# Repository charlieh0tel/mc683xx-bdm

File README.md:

# mc683xx-bdm

A USB background debug mode (BDM) pod for Motorola CPU32
microcontrollers (683xx), such as the MC68331. A Raspberry Pi Pico on a
small carrier board drives the standard 10-pin BDM header through 5 V
level translators. Firmware and host tools are in Rust.

- Reset, halt, run and step the target; read and write its registers
  and memory.
- Debug with gdb: breakpoints, stepping, Ctrl-C.
- Script it from Python, flash programming included.
- Read 512 KB in under 6 seconds.

Proven on an MC68331 from a Linux host; see [docs/status.md](docs/status.md)
for what works, what is untried, and the limits.

## Quickstart

1. Install `bdm`, the udev rule and the firmware, from the
   [APT repository](https://github.com/charlieh0tel/apt-repo)
   (`sudo apt-get install mc683xx-bdm`) or a GitHub Release's `.deb`.
2. Flash the firmware: `bdm bootsel`, then copy
   `/usr/share/mc683xx-bdm/pod-fw-rp2040.uf2` onto the RPI-RP2 drive.
3. Cable the pod to the target's BDM header and power the target.
4. Run `bdm pins`, `bdm reset`, then `bdm regs`.

Don't unplug the pod while its green LED is lit.

## Install

```
sudo apt-get install mc683xx-bdm   # bdm, the udev rule, the UF2
cargo install mc683xx-bdm          # bdm only
pip install mc683xx-bdm            # the Python module mc683xx_bdm
```

Without the Debian package, install the udev rule by hand
([docs/usage.md](docs/usage.md)).

## Documentation

- [docs/usage.md](docs/usage.md): `bdm`, gdb, Python, udev.
- [docs/status.md](docs/status.md): what works, limits, getting a board.
- [docs/development.md](docs/development.md): layout, building, testing.
- [docs/usb-protocol.md](docs/usb-protocol.md): the host-pod protocol.
- [docs/bring-up.md](docs/bring-up.md): checking a new pod.
- [hardware/README.md](hardware/README.md): the carrier's revisions.
- [PLAN.md](PLAN.md): the design and why.

## License

Hardware (`hardware/`): CERN-OHL-S-2.0. Everything else of the
project's own: GPL-3.0-only. `third_party/` documents are their
owners' (`third_party/NOTICE`).

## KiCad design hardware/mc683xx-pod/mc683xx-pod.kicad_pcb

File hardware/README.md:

# Hardware

`mc683xx-pod/` is the carrier board's KiCad project.  `production/`
holds each release as fabricated; it is not changed afterwards.

## Revisions

| Rev | Release | PCB | Assembly |
|---|---|---|---|
| 0.1 | `production/20261102-0.1/` | as 0.2 | A1 (Pico) not in the BOM, hand-soldered; J2 (SWD) fitted |
| 0.2 | `production/20261102-0.2/` | as 0.1 | A1 placed by JLCPCB (LCSC C9900019762); J2 not fitted |

0.1 and 0.2 are one PCB: their Gerbers and drill files match, apart
from creation dates.  The revision differs only in the BOM, the
placement file and the title blocks.  The silkscreen of both reads
"mc683xx-pod rev 0.1", since the silkscreen text was not bumped for
0.2.  A board with a Pico but no J2 is a 0.2.

## Next revision

Changes for the carrier after 0.2.  None is needed for 0.2 to work;
each fixes something seen on the bench.

1. BKPT released whatever the Pico does.  A Pico reset or power loss
   while U1 is enabled can glitch BKPT (`docs/bring-up.md`, step 5):
   GP9, U1's input, falls through R15 and the RP2040's pull-down in
   about 0.3 us, before Q3's gate, through its 100k, turns U1 off in
   about 1-2 us; U1 drives BKPT low, then R3 pulls it high, one DSCLK
   clock to a halted CPU.  The firmware keeps U1 off while idle, which
   leaves only a reset mid-request or during `hold`.  Fix: drive U1's
   input through an inverting stage like Q3's, a BSS138BK with its
   gate on GP9 (100k gate pull-down) and its drain on U1's input with
   a 2.2k pull-up to target VDD; R15 goes.  Every state that leaves
   GP9 undriven or low (reset, boot, power loss, unpowered) then holds
   U1's input high, BKPT released, whatever U1's enable does.  The
   firmware inverts GP9 (its pad's output override).  Check: the
   stage's edges at 4 MHz DSCLK (about 20 ns into U1's input and the
   FET's output capacitance) and 2.3 mA from VDD while DSCLK is low.
2. Silkscreen revision text bumped with the title blocks
   (`AGENTS.md`, Hardware).
3. Status LEDs on the carrier, visible with the Pico mounted (a pod
   in a case may hide the Pico's GP25 LED, lit while U1 is on).
   Required: target VDD, lit while the target is powered.  Either
   wired straight from target VDD (works with the pod unpowered; loads
   target VDD a few mA) or driven by the firmware from the VDD sense
   reading (no load on the target; needs a spare GPIO).  Optional, on
   one or two more LEDs (mono, bicolor or tricolor, not decided),
   driven by the firmware from spare GPIOs: target halted (FREEZE
   high) or running (FREEZE low, also with no target); safe or not
   safe to remove (U1 off or on).  Pins: one GPIO per LED or color,
   from the spare GPIOs (GP0, GP1, GP13-GP22, GP27, GP28; PLAN.md, pin
   table).  With item 1's inverting stage a replug is always safe, so
   that indication could show activity or errors instead.

`fastcheck.py` reports on the BDM link's fast nets
(`uv run python fastcheck.py mc683xx-pod/mc683xx-pod.kicad_pcb`).
`make render` (repository root) rebuilds `docs/images/mc683xx-pod-top.png`
from the board file.

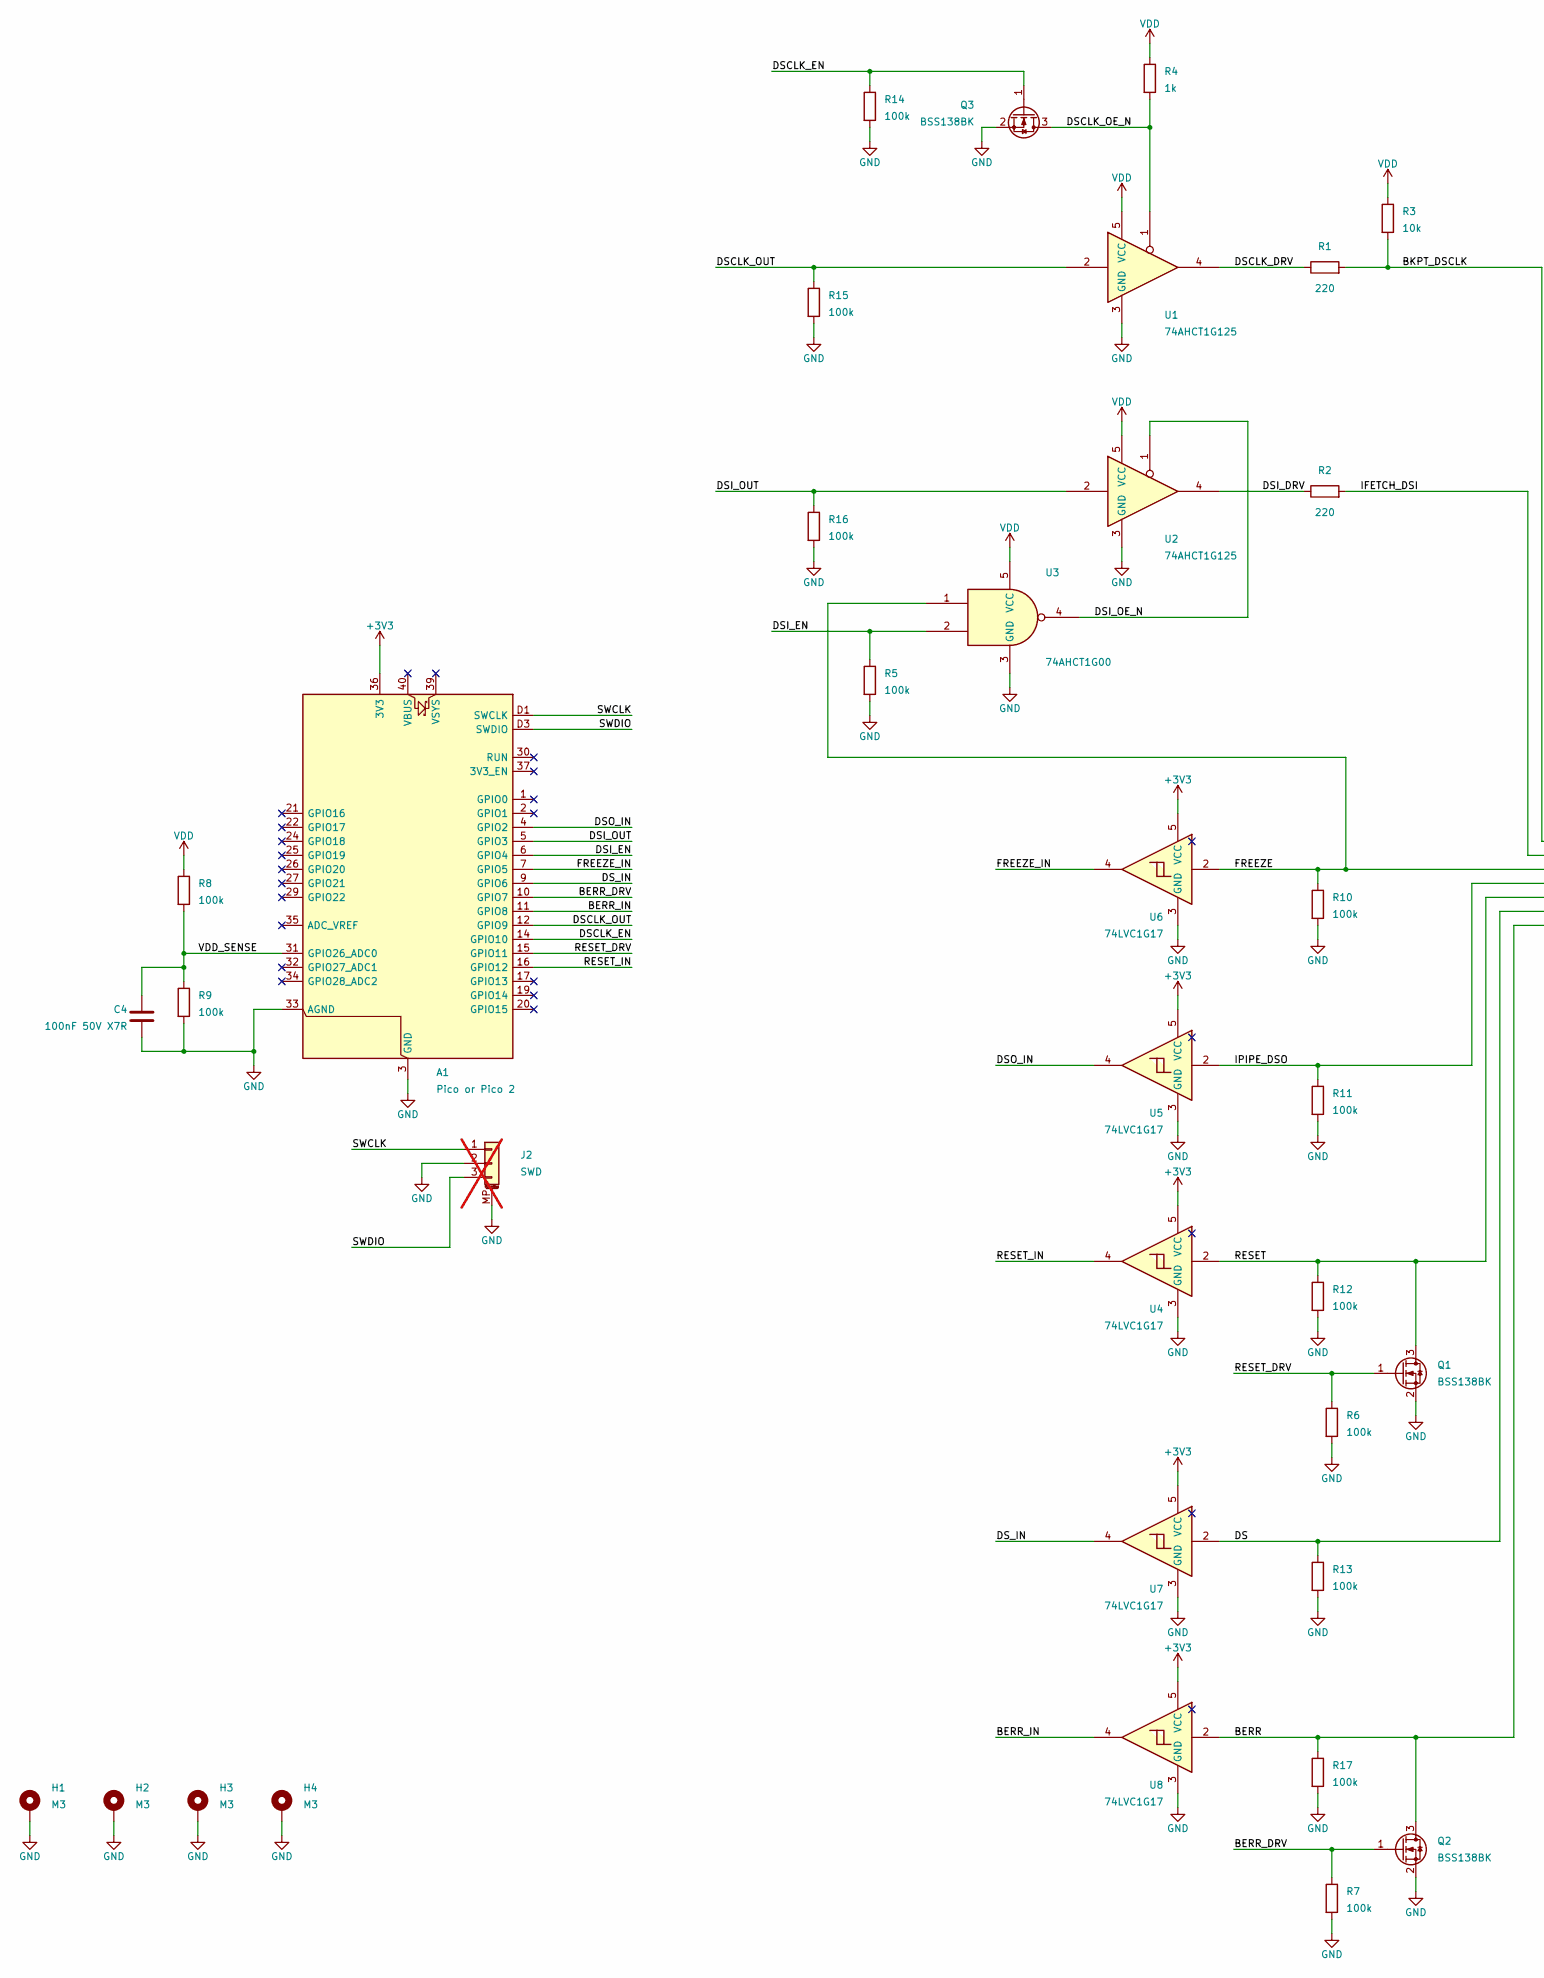
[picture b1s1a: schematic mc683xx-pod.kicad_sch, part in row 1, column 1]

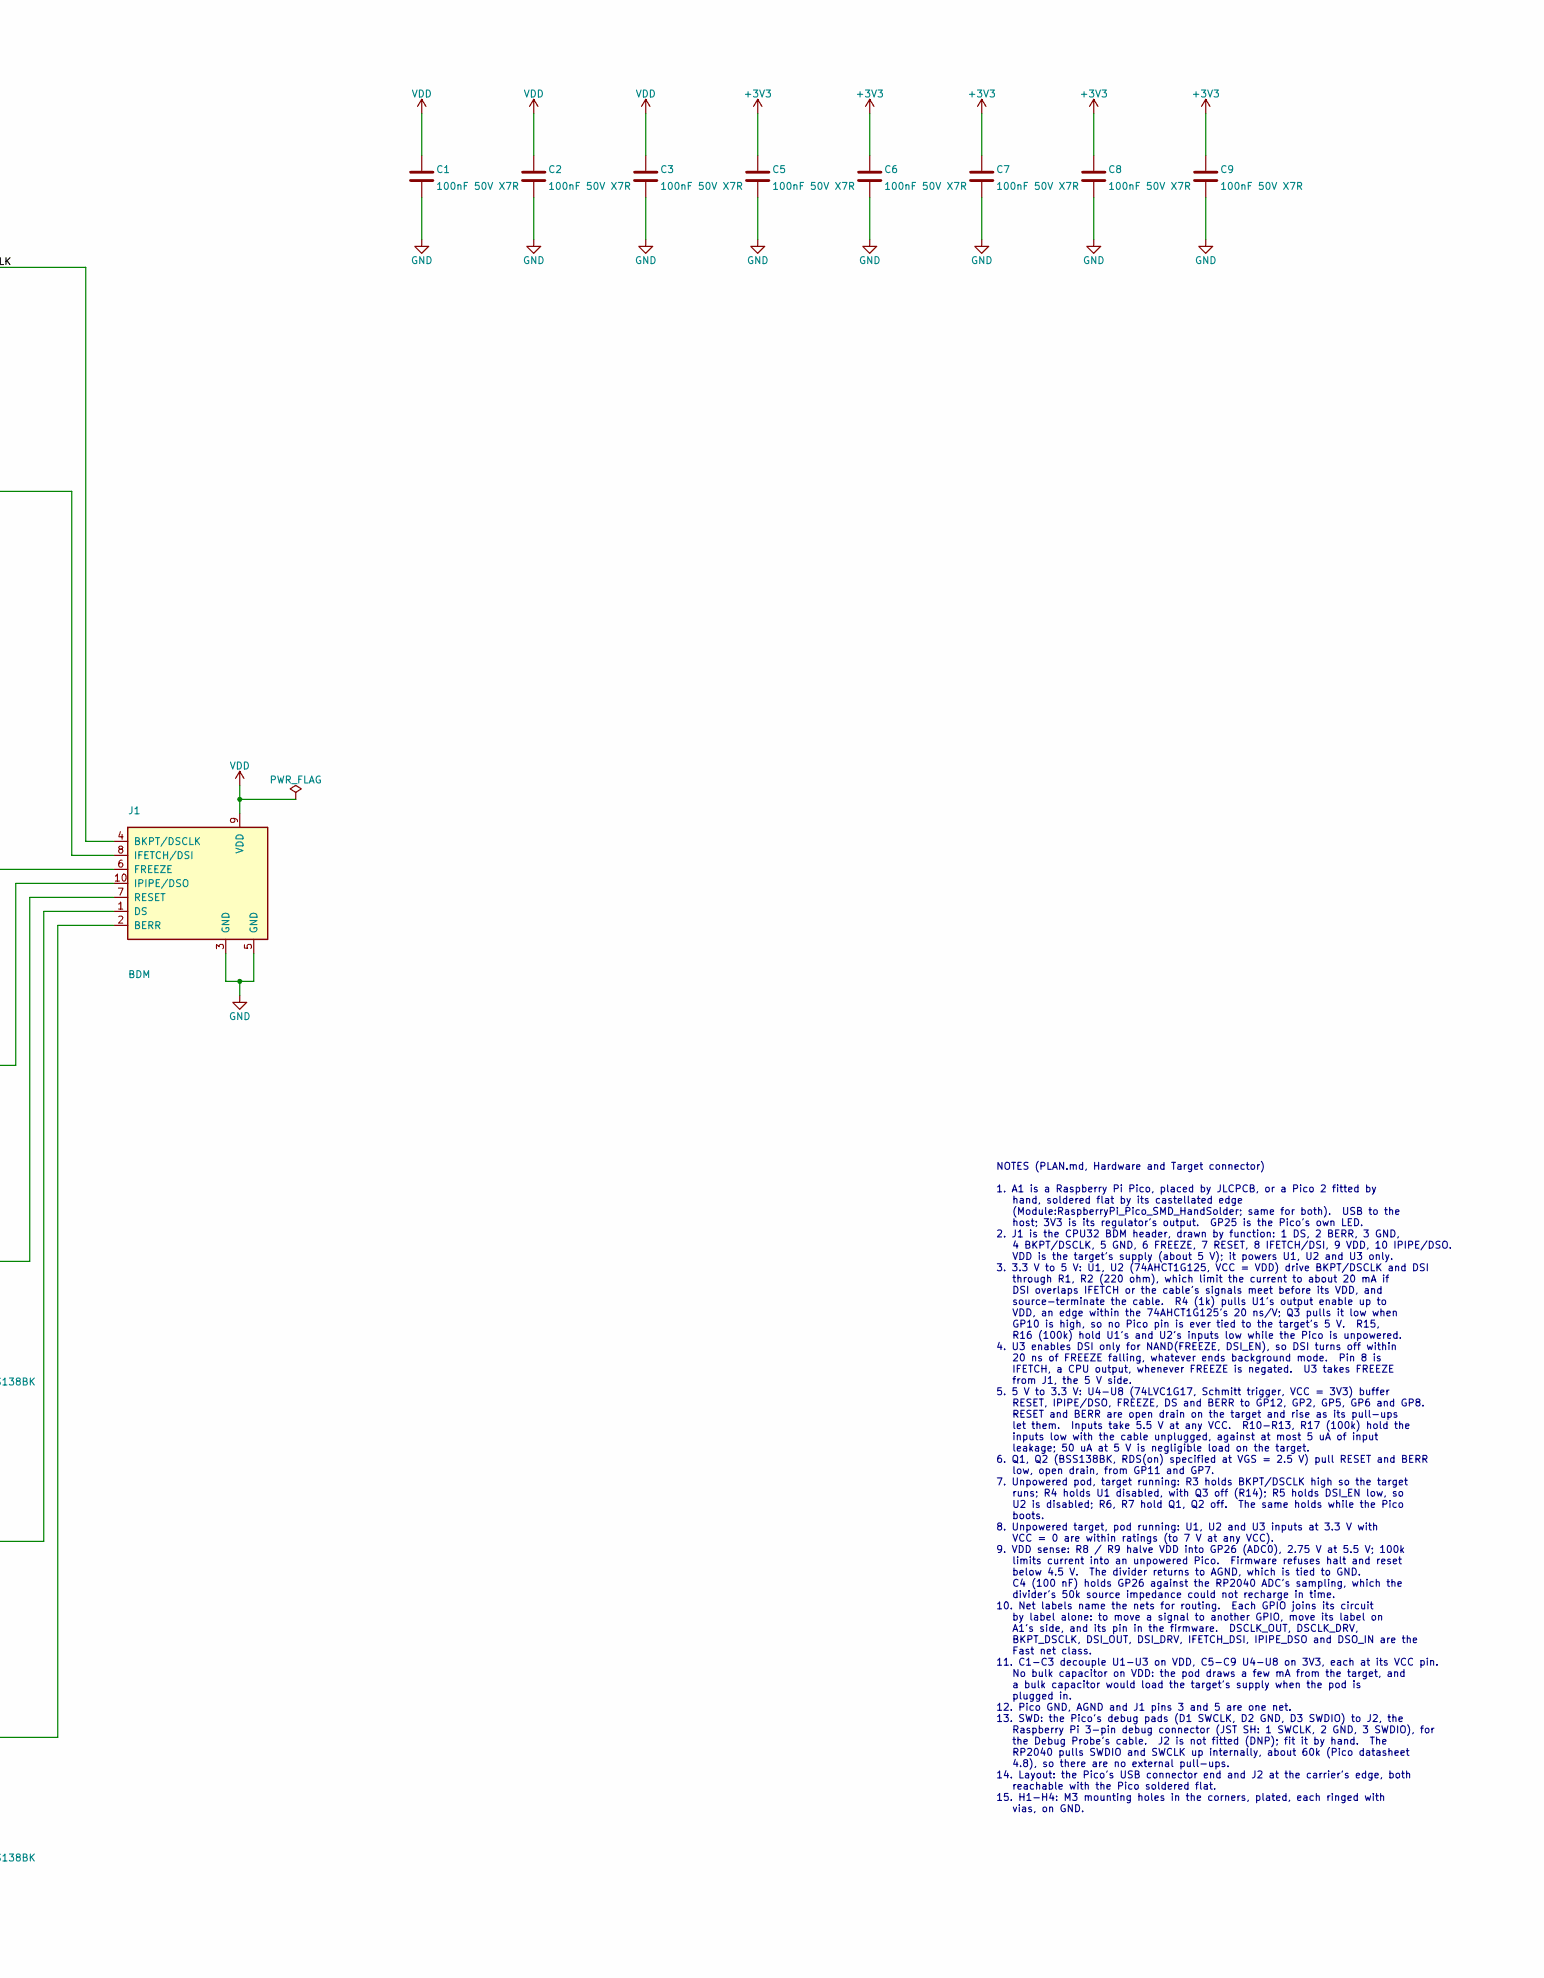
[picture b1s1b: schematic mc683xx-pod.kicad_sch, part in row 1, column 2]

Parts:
A1: Pico or Pico 2; RaspberryPi_Pico_SMD_HandSolder; MPN SC0915; LCSC C9900019762
C1, C2, C3, C4, C5, C6, C7, C8, C9: 100nF 50V X7R; C_0603_1608Metric; MPN CC0603KRX7R9BB104; LCSC C14663
H1, H2, H3, H4: M3; MountingHole_3.2mm_M3_Pad_Via
J1: BDM; IDC-Header_2x05_P2.54mm_Vertical; MPN 2.54-2*5P; LCSC C5665
J2: SWD; JST_SH_SM03B-SRSS-TB_1x03-1MP_P1.00mm_Horizontal; MPN SM03B-SRSS-TB(LF)(SN); LCSC C160403; not fitted
Q1, Q2, Q3: BSS138BK; SOT-23; MPN BSS138BK,215; LCSC C282529
R1, R2: 220; R_0603_1608Metric; MPN 0603WAF2200T5E; LCSC C22962
R3: 10k; R_0603_1608Metric; MPN 0603WAF1002T5E; LCSC C25804
R4: 1k; R_0603_1608Metric; MPN 0603WAF1001T5E; LCSC C21190
R5, R6, R7, R8, R9, R10, R11, R12, R13, R14, R15, R16, R17: 100k; R_0603_1608Metric; MPN 0603WAF1003T5E; LCSC C25803
U1, U2: 74AHCT1G125; SOT-23-5; MPN SN74AHCT1G125DBVR; LCSC C7484
U3: 74AHCT1G00; SOT-23-5; MPN SN74AHCT1G00DBVR; LCSC C473380
U4, U5, U6, U7, U8: 74LVC1G17; SOT-23-5; MPN SN74LVC1G17DBVR; LCSC C7836

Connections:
+3V3: A1.36 (3V3), C5.1, C6.1, C7.1, C8.1, C9.1, U4.5 (VCC), U5.5 (VCC), U6.5 (VCC), U7.5 (VCC), U8.5 (VCC)
/BERR: J1.2 (BERR), Q2.3 (D), R17.1, U8.2
/BERR_DRV: A1.10 (GPIO7), Q2.1 (G), R7.1
/BERR_IN: A1.11 (GPIO8), U8.4
/BKPT_DSCLK: J1.4 (BKPT/DSCLK), R1.2, R3.2
/DS: J1.1 (DS), R13.1, U7.2
/DSCLK_DRV: R1.1, U1.4
/DSCLK_EN: A1.14 (GPIO10), Q3.1 (G), R14.1
/DSCLK_OE_N: Q3.3 (D), R4.2, U1.1
/DSCLK_OUT: A1.12 (GPIO9), R15.1, U1.2
/DSI_DRV: R2.1, U2.4
/DSI_EN: A1.6 (GPIO4), R5.1, U3.2
/DSI_OE_N: U2.1, U3.4
/DSI_OUT: A1.5 (GPIO3), R16.1, U2.2
/DSO_IN: A1.4 (GPIO2), U5.4
/DS_IN: A1.9 (GPIO6), U7.4
/FREEZE: J1.6 (FREEZE), R10.1, U3.1, U6.2
/FREEZE_IN: A1.7 (GPIO5), U6.4
/IFETCH_DSI: J1.8 (IFETCH/DSI), R2.2
/IPIPE_DSO: J1.10 (IPIPE/DSO), R11.1, U5.2
/RESET: J1.7 (RESET), Q1.3 (D), R12.1, U4.2
/RESET_DRV: A1.15 (GPIO11), Q1.1 (G), R6.1
/RESET_IN: A1.16 (GPIO12), U4.4
/SWCLK: A1.D1 (SWCLK), J2.1
/SWDIO: A1.D3 (SWDIO), J2.3
/VDD_SENSE: A1.31 (GPIO26_ADC0), C4.1, R8.2, R9.1
GND: A1.3 (GND), A1.8 (GND), A1.13 (GND), A1.18 (GND), A1.23 (GND), A1.28 (GND), A1.33 (AGND), A1.38 (GND), A1.D2 (GND), C1.2, C2.2, C3.2, C4.2, C5.2, C6.2, C7.2, C8.2, C9.2, H1.1 (1_1), H2.1 (1_1), H3.1 (1_1), H4.1 (1_1), J1.3 (GND), J1.5 (GND), J2.2, J2.MP (MountPin), Q1.2 (S), Q2.2 (S), Q3.2 (S), R5.2, R6.2, R7.2, R9.2, R10.2, R11.2, R12.2, R13.2, R14.2, R15.2, R16.2, R17.2, U1.3 (GND), U2.3 (GND), U3.3 (GND), U4.3 (GND), U5.3 (GND), U6.3 (GND), U7.3 (GND), U8.3 (GND)
VDD: C1.1, C2.1, C3.1, J1.9 (VDD), R3.1, R4.1, R8.1, U1.5 (VCC), U2.5 (VCC), U3.5 (VCC)

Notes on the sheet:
NOTES (PLAN.md, Hardware and Target connector) 1. A1 is a Raspberry Pi Pico, placed by JLCPCB, or a Pico 2 fitted by hand, soldered flat by its castellated edge (Module:RaspberryPi_Pico_SMD_HandSolder; same for both). USB to the host; 3V3 is its regulator's output. GP25 is the Pico's own LED. 2. J1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

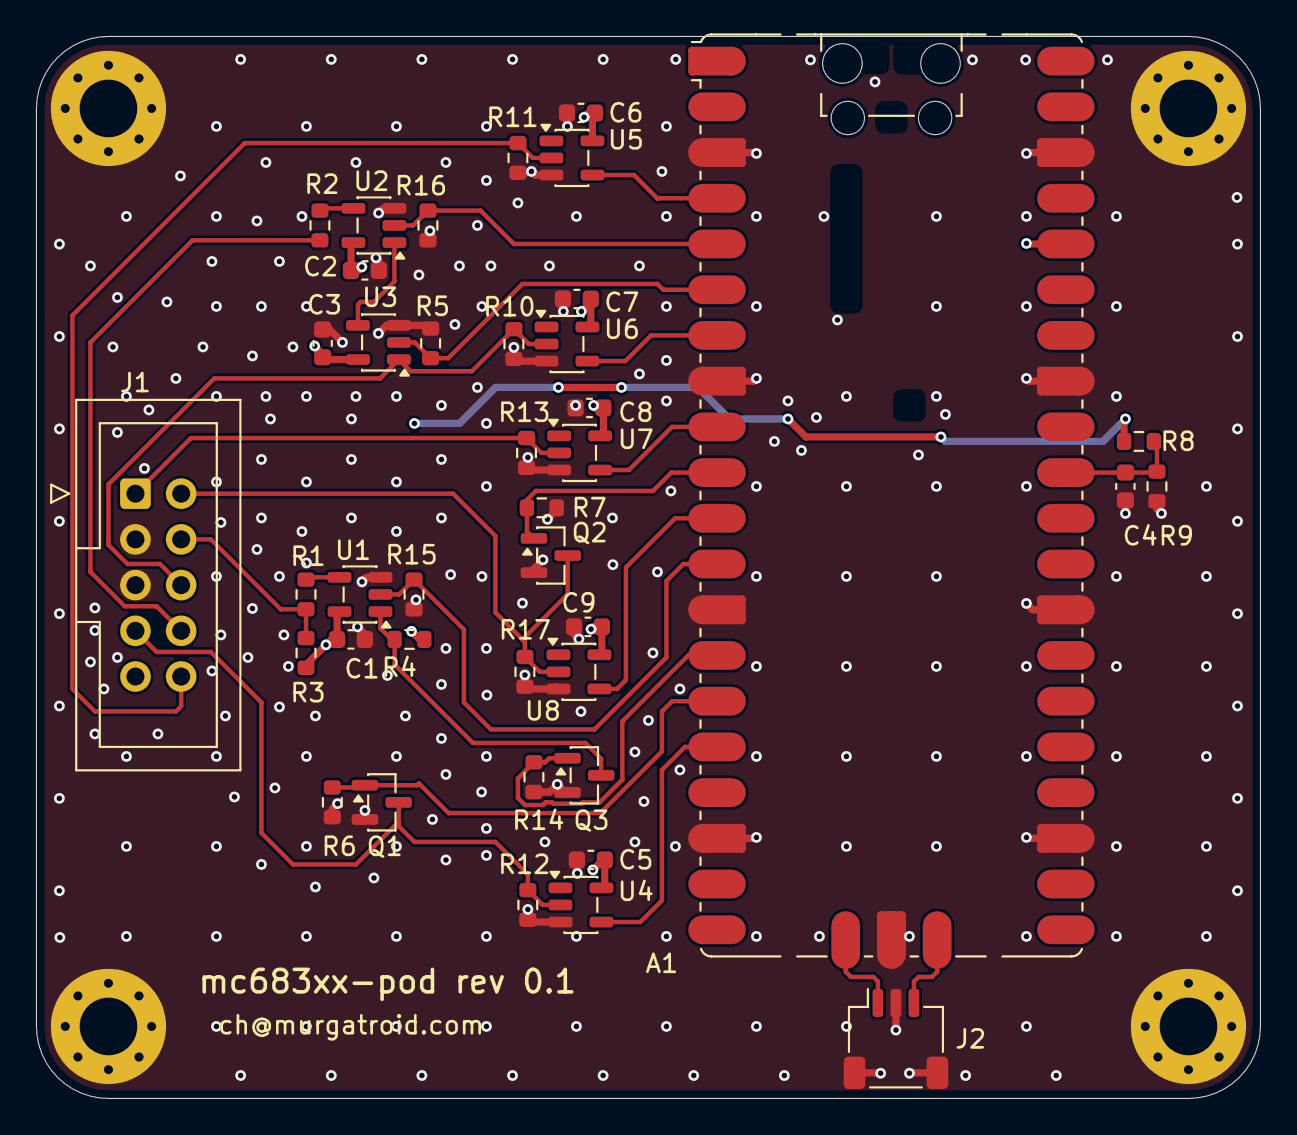
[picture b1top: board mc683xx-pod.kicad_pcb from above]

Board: 4 copper layers, 68.0 x 59.0 mm, 44 parts (0 on the bottom side), 28 nets.

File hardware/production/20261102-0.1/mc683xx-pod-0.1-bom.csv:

Comment,Designator,Footprint,LCSC Part #
100nF 50V X7R,"C1,C2,C3,C4,C5,C6,C7,C8,C9",C_0603_1608Metric,C14663
BDM,J1,IDC-Header_2x05_P2.54mm_Vertical,C5665
SWD,J2,JST_SH_SM03B-SRSS-TB_1x03-1MP_P1.00mm_Horizontal,C160403
BSS138BK,"Q1,Q2,Q3",SOT-23,C282529
220,"R1,R2",R_0603_1608Metric,C22962
10k,R3,R_0603_1608Metric,C25804
1k,R4,R_0603_1608Metric,C21190
100k,"R5,R6,R7,R8,R9,R10,R11,R12,R13,R14,R15,R16,R17",R_0603_1608Metric,C25803
74AHCT1G125,"U1,U2",SOT-23-5,C7484
74AHCT1G00,U3,SOT-23-5,C473380
74LVC1G17,"U4,U5,U6,U7,U8",SOT-23-5,C7836

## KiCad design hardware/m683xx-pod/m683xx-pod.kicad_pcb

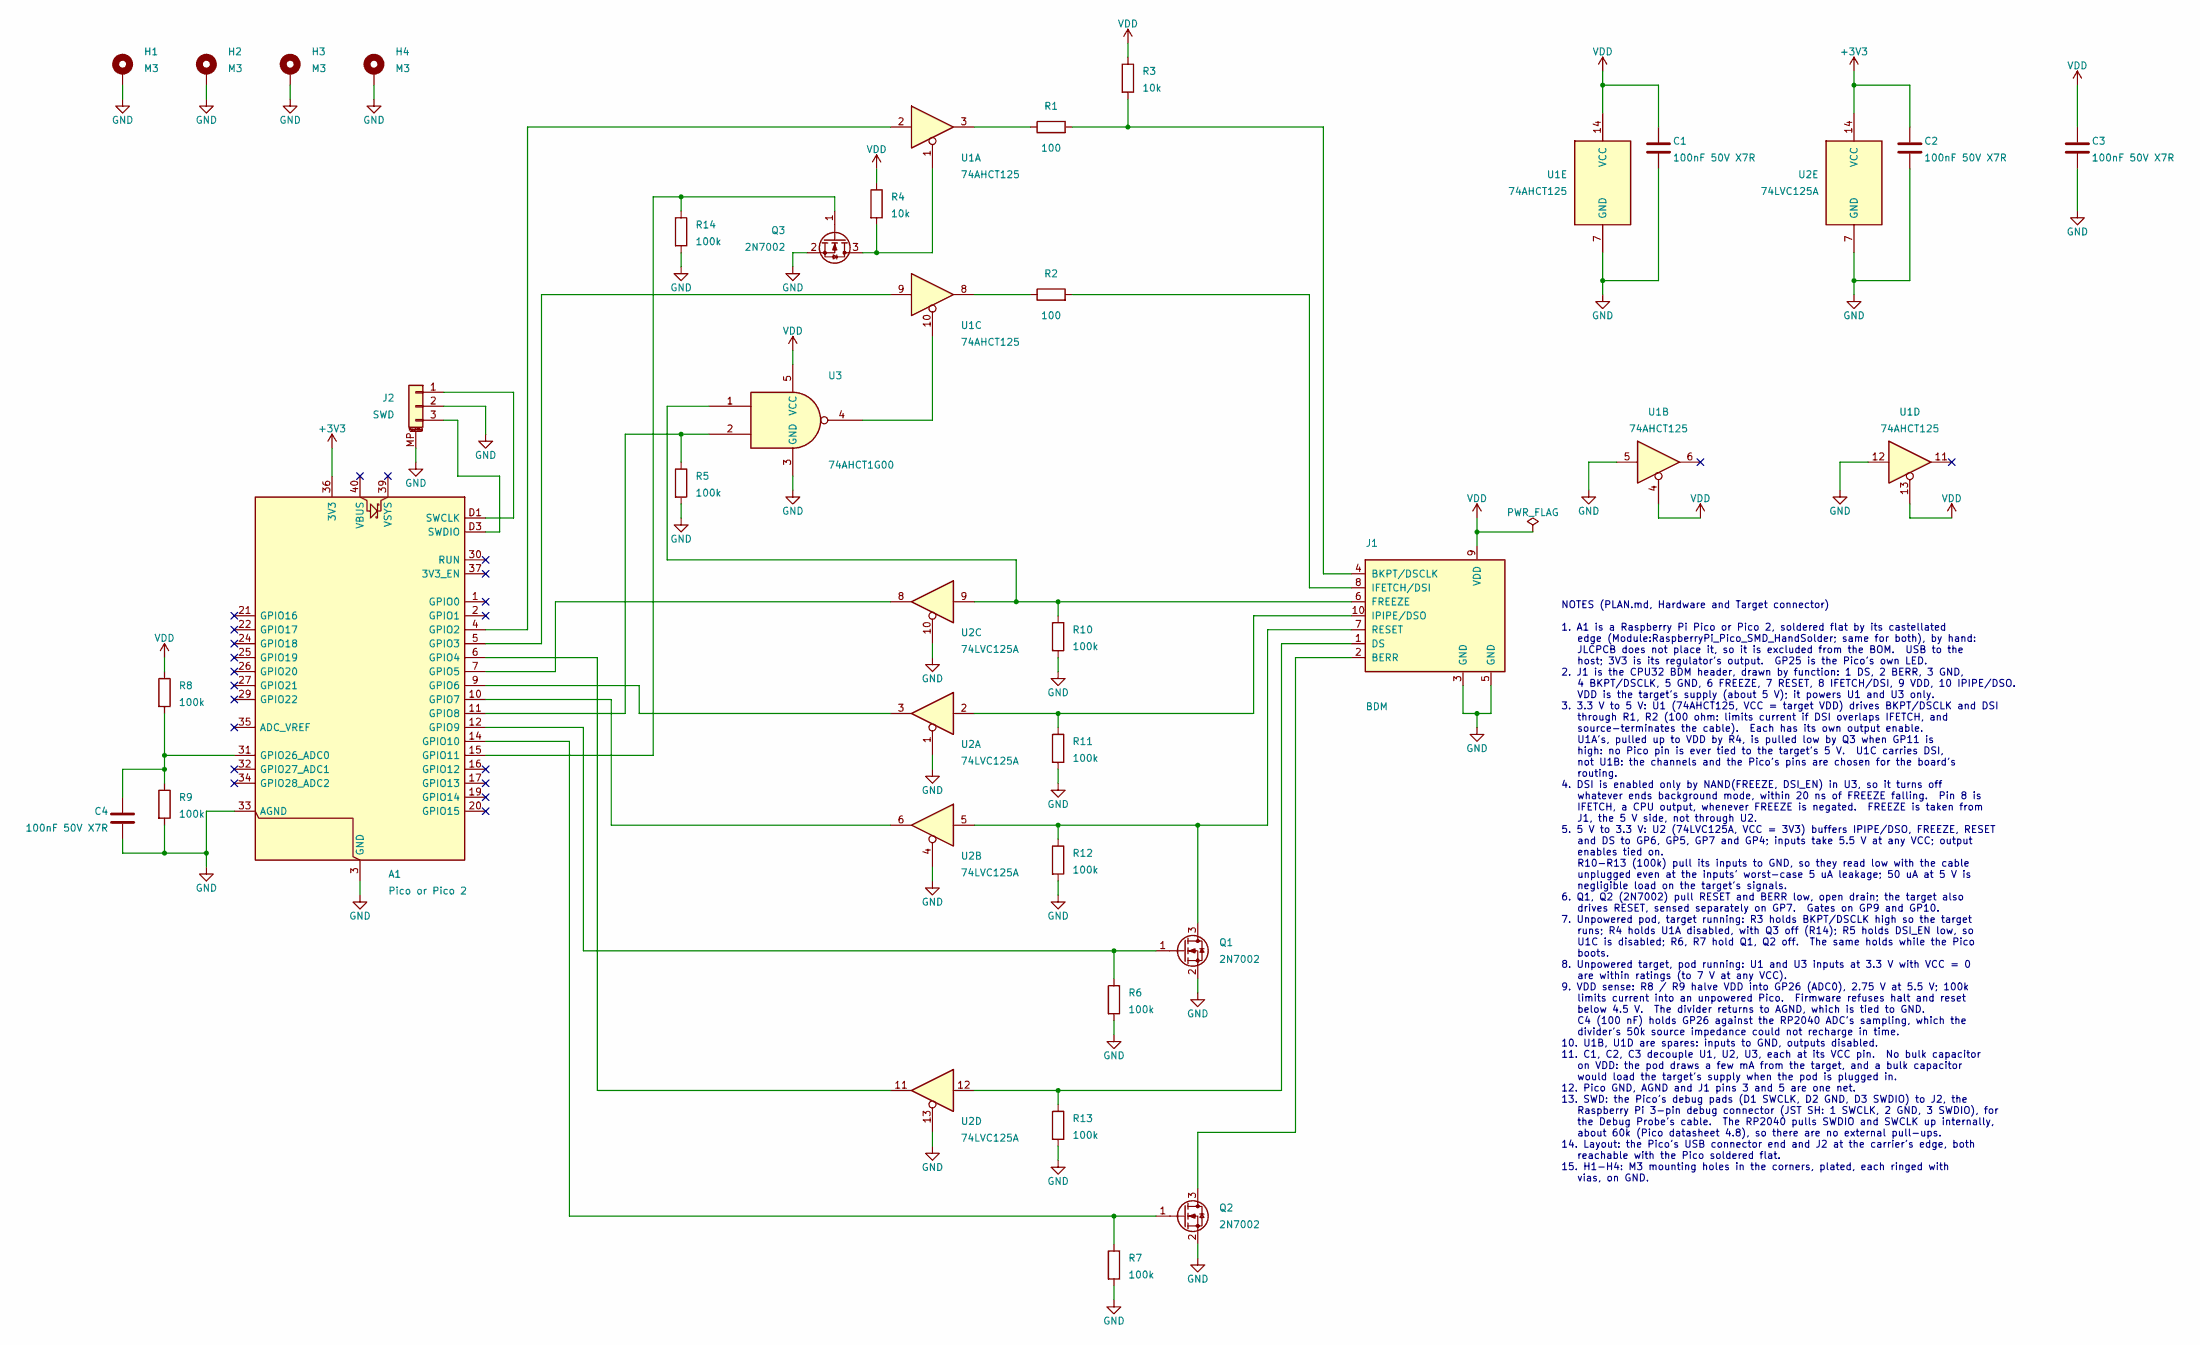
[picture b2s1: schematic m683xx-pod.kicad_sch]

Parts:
A1: Pico or Pico 2; RaspberryPi_Pico_SMD_HandSolder; MPN SC0915
C1, C2, C3, C4: 100nF 50V X7R; C_0603_1608Metric; MPN CC0603KRX7R9BB104; LCSC C14663
H1, H2, H3, H4: M3; MountingHole_3.2mm_M3_Pad_Via
J1: BDM; IDC-Header_2x05_P2.54mm_Vertical; MPN 2.54-2*5P; LCSC C5665
J2: SWD; JST_SH_SM03B-SRSS-TB_1x03-1MP_P1.00mm_Horizontal; MPN SM03B-SRSS-TB(LF)(SN); LCSC C160403
Q1, Q2, Q3: 2N7002; SOT-23; MPN 2N7002; LCSC C8545
R1, R2: 100; R_0603_1608Metric; MPN 0603WAF1000T5E; LCSC C22775
R3, R4: 10k; R_0603_1608Metric; MPN 0603WAF1002T5E; LCSC C25804
R5, R6, R7, R8, R9, R10, R11, R12, R13, R14: 100k; R_0603_1608Metric; MPN 0603WAF1003T5E; LCSC C25803
U1: 74AHCT125; TSSOP-14_4.4x5mm_P0.65mm; MPN SN74AHCT125PWR; LCSC C36365
U2: 74LVC125A; TSSOP-14_4.4x5mm_P0.65mm; MPN SN74LVC125APWR; LCSC C7813
U3: 74AHCT1G00; SOT-23-5; MPN SN74AHCT1G00DBVR; LCSC C473380

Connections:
+3V3: A1.36 (3V3), C2.1, U2.14 (VCC)
GND: A1.3 (GND), A1.8 (GND), A1.13 (GND), A1.18 (GND), A1.23 (GND), A1.28 (GND), A1.33 (AGND), A1.38 (GND), A1.D2 (GND), C1.2, C2.2, C3.2, C4.2, H1.1, H2.1, H3.1, H4.1, J1.3 (GND), J1.5 (GND), J2.2, J2.MP (MountPin), Q1.2 (S), Q2.2 (S), Q3.2 (S), R5.2, R6.2, R7.2, R9.2, R10.2, R11.2, R12.2, R13.2, R14.2, U1.5, U1.7 (GND), U1.12, U2.1, U2.4, U2.7 (GND), U2.10, U2.13, U3.3 (GND)
unnamed: A1.4 (GPIO2), U1.2
unnamed: A1.5 (GPIO3), U1.9
unnamed: A1.6 (GPIO4), U2.11
unnamed: A1.7 (GPIO5), U2.8
unnamed: A1.9 (GPIO6), U2.3
unnamed: A1.10 (GPIO7), U2.6
unnamed: A1.11 (GPIO8), R5.1, U3.2
unnamed: A1.12 (GPIO9), Q1.1 (G), R6.1
unnamed: A1.14 (GPIO10), Q2.1 (G), R7.1
unnamed: A1.15 (GPIO11), Q3.1 (G), R14.1
unnamed: A1.31 (GPIO26_ADC0), C4.1, R8.2, R9.1
unnamed: A1.D1 (SWCLK), J2.1
unnamed: A1.D3 (SWDIO), J2.3
unnamed: J1.2 (BERR), Q2.3 (D)
unnamed: J1.4 (BKPT/DSCLK), R1.2, R3.2
unnamed: J1.1 (DS), R13.1, U2.12
unnamed: J1.6 (FREEZE), R10.1, U2.9, U3.1
unnamed: J1.8 (IFETCH/DSI), R2.2
unnamed: J1.10 (IPIPE/DSO), R11.1, U2.2
unnamed: J1.7 (RESET), Q1.3 (D), R12.1, U2.5
unnamed: Q3.3 (D), R4.2, U1.1
unnamed: R1.1, U1.3
unnamed: R2.1, U1.8
unnamed: U1.10, U3.4
VDD: C1.1, C3.1, J1.9 (VDD), R3.1, R4.1, R8.1, U1.4, U1.13, U1.14 (VCC), U3.5 (VCC)

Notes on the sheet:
NOTES (PLAN.md, Hardware and Target connector) 1. A1 is a Raspberry Pi Pico or Pico 2, soldered flat by its castellated edge (Module:RaspberryPi_Pico_SMD_HandSolder; same for both), by hand: JLCPCB does not place it, so it is excluded from the BOM. USB to the host; 3V3 is its regulator's output. GP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

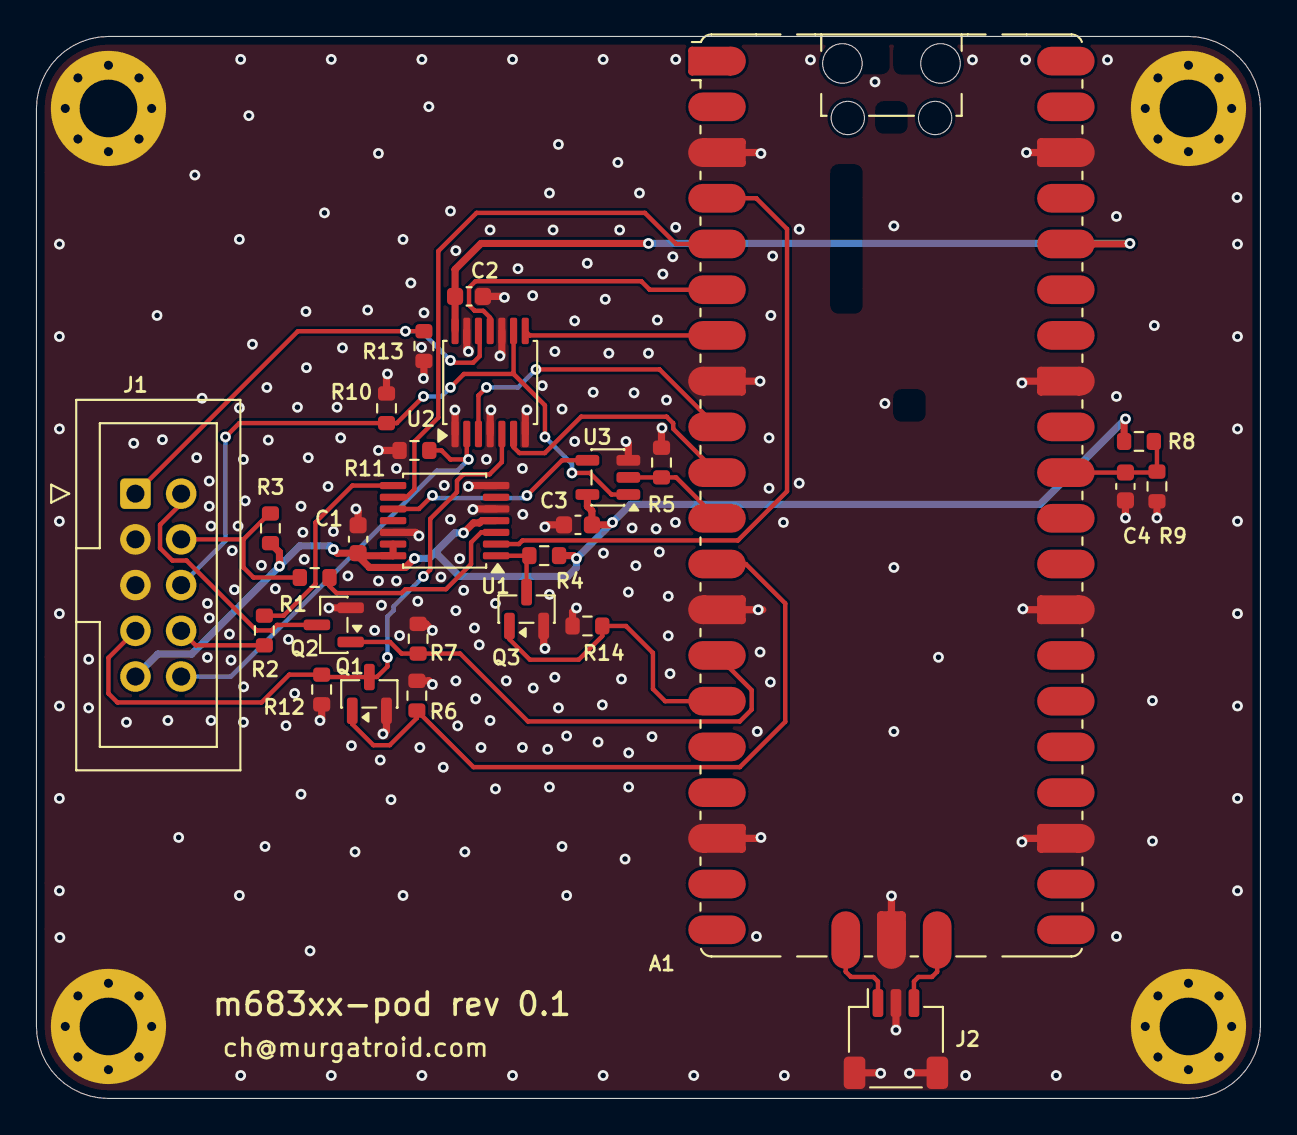
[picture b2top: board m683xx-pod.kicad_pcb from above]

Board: 2 copper layers, 68.0 x 59.0 mm, 31 parts (0 on the bottom side), 27 nets.
